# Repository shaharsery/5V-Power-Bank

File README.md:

# 5V rechargeable power bank (Work in progress)

This project is a 5V rechargeable power bank, intended for use with 1 Li-ion / Li-Pol 3.7V rechargeable battery cell.

The design supports up to 1A of charge current and up to 1A of output current.

The exact specification of this design are strongly related to the battery used and other elements such as components used, enclosure, wall adapter etc. 

This is an open source hardware (OSHW) project, licensed under the Creative Commons Attribution Share Alike 4.0 International license.
 
For more information read the LICENSE file in the master branch, and visit [creativecommons.org](https://creativecommons.org/)

**Please note that this project has not yet been manufactured or tested! USE AT YOUR OWN RISK!**

## Specifications 

#### Nominal ratings and parameters: 

Input Voltage: 5V

Output Voltage: 5V

Battery Cell: Li-ion / Li-Pol 3.7V 

Charge Current: 1A MAX (Adjustable)

Output Current: 1A MAX

#### Features:

The features below are based on the full BOM (without NC components), changing values of components and / or unplacing components may cause unintended behaviors.

\- Input connectors: USB Type-B Micro, solder pads.

\- Output connectors: USB Type-A port, solder pads. 

\- Battery cell protections: Overcharge voltage, overdischarge voltage, overcharge current, overdischarge current, over-temperature operation, ESD protection and reverse polarity protection.

** THIS DOESN'T MEAN NOTHING CAN GO WRONG, ALWAYS MAKE SURE YOU CONNECTED EVERYTHING CORRECTLY, BATTERIES CAN EXPLODE, BURN AND HARM YOU IF NOT PROPERLY USED **

\- Adjustable charge current by changing resistor value (R5)

\- 2 indication LEDs:

- Green LED to indicate charge completed (the green LED will turn off once the battery cell entered 2nd charge cycle).
	
- Blue LED to indicate input power to the PCB. 

Both LEDs will turn off when the power bank is removed from the wall adapter.

\- If the device is connected to a wall adapter a battery and a load, the load will be powered from the wall adapter and the battery will keep on charging, this might not work properly if the wall adapter rated current is not high enough (for MAX currents, the wall adapter should be capable of driving at least 2A)

## Notes

\- The design was created as an entry level design project, it was designed to allow for others to learn, work with and create.
 I wanted to keep the design pretty simple and to make it 'hand-solderable', that's why all passive components' packages are 0603 or larger and all ICs have lead pins,
 that way all components can be soldered using a solder iron and some basic skills.
 
 \- Through the design process I was aiming for the use of 18650 Li-ion battery cells, though it should work with any Li-ion / Li-Pol 3.7V battery, I plan on testing other battery cell packages once I'll have the PCBs for prototyping.
 
 \- Though all the components used in this project can be easily sourced from Digi-Key and Mouser, I tried to use components that can also be sourced through LCSC, Ebay or AliExpress, try to find a reliable distributor that suits your costs and needs.
 
 \- A lot of modifications can be made to reduce the cost of this design, consider the necessity of components according to your own use.
 
 \- I know some people would prefer the input connector to be Type-C, I might add another version of this design with Type-C connector later.
 
 \- I plan on creating 2 types of PCBs, one roughly the dimensions of a 18650 package, and one compact design that might be more suitable for flat battery packages.
 
 \- Please feel free to contact me if you have any question or remark, or if you found any mistake. I'll try to reply as fast as I can but I can't promise anything.
 
 \- Keep being awesome and help the OSHW community grow!

## Disclaimer

**Before you work with this project in any way, please make sure you understand what you are doing, electronics and batteries can be harmful and dangerous when not used properly.** 

**By using this project in any way you agree that you are using it at your own risk and you can't hold any one else accountable for any damage or harm that might be caused due to your use of this project.**

**Please note that this project has not yet been manufactured or tested! USE AT YOUR OWN RISK!**

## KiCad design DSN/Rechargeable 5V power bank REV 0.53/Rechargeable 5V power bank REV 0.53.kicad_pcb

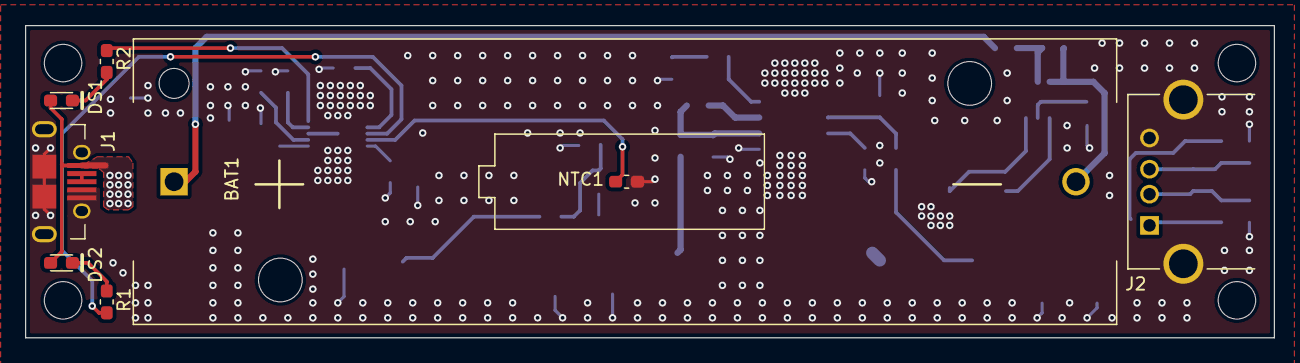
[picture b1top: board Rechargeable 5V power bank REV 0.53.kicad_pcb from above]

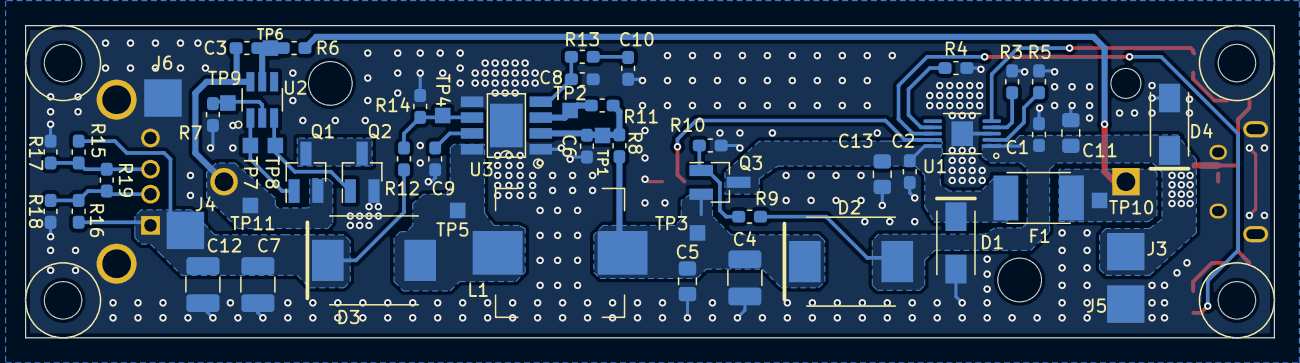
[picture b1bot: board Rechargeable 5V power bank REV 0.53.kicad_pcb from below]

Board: 2 copper layers, 100.0 x 25.0 mm, 69 parts (61 on the bottom side), 31 nets.

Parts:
BAT1: BAT_18650_HOLDER_THT
C1, C2, C6: CAPC_1uF_0603; CACP_0603_HandSolder
C3: CAPC_100nF_0603; CACP_0603_HandSolder
C4: CAPC_22uF_1210; CAPC_1210_HandSolder
C5, C11, C13: CAPC_10uF_0805; CAPC_0805_HandSolder
C7, C12: CAPC_10uF_1210; CAPC_1210_HandSolder
C8: CAPC_47pF_0603; CACP_0603_HandSolder
C9: CAPC_10nF_0603; CACP_0603_HandSolder
C10: CAPC_2.2nF_0603; CACP_0603_HandSolder
D1, D4: TVS_5V_9.2V_DO214AC; DO-214AC
D2, D3: Schottky_40V_5A_DO-214AB; DO-214AB
DS1: LEDC_BLUE_0603; LEDC_0603_HandSolder
DS2: LEDC_GREEN_0603; LEDC_0603_HandSolder
F1: PTC_POLYFUSE_8V_2A_1812; POLYFUSEC_1812
J1: Micro_USB_CONN; USB-TYPE-B_CONN_PORT
J2: USB-A_CONN; USB-TYPE-A_CONN_PORT
J3, J4, J5, J6: 1POS_CONN_PAD_30X30MM_H1MM; PAD_RECT_30X30
L1: INDC_10uH_CDRH104R; CDRH104R
MH1, MH2, MH3, MH4: M3C6_NP
NTC1: NTC_10K_3380K_0603; RESC_0603_HandSolder
Q1, Q2: NMOS_20V_3.6A_SOT-23-3; SOT-23_Handsoldering
Q3: PMOS_20V_4.2A_SOT-23-3; SOT-23_Handsoldering
R1, R2: RESC_470R_0603; RESC_0603_HandSolder
R3: RESC_2K_0603; RESC_0603_HandSolder
R4, R10, R11, R14, R15, R16, R17, R18: RESC_10K_0603; RESC_0603_HandSolder
R5: RESC_549R_0603; RESC_0603_HandSolder
R6: RESC_330R_0603; RESC_0603_HandSolder
R7: RESC_2K7_0603; RESC_0603_HandSolder
R8: RESC_10R_0603; RESC_0603_HandSolder
R9: RESC_1K_0603; RESC_0603_HandSolder
R12: RESC_30K1_0603; RESC_0603_HandSolder
R13: RESC_51K_0603; RESC_0603_HandSolder
R19: RESC_0R_0603; RESC_0603_HandSolder
TP1, TP2, TP3, TP4, TP5, TP6, TP7, TP8, TP9, TP10, TP11: TP_1.25X1.25_MM; TP_RECT_1.25X1.25
U1: BQ24090DGQR; BQ24090DGQR_MSOP-10
U2: AP9101C; AP9101C_SOT-23-6_Handsoldering
U3: PAM2421; PAM2421_SOIC-8-EP

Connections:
+VBAT_CELL: C2.2, C13.1, D1.K, F1.2, Q3.D, U1.10
/+VBAT: BAT1.+, F1.1, R6.2, TP10.1
/-VBAT: BAT1.-, C3.2, Q1.S, TP11.1, U2.6
/BLED: DS1.K, R2.2
/BOOST_COMP: C8.1, R13.1, U3.4
/BOOST_EN: R11.2, TP2.1, U3.3
/BOOST_FB: R12.2, R14.2, TP4.1, U3.6
/BOOST_IND: C4.1, C5.1, D2.K, L1.1, Q3.S, R8.1, TP3.1
/BOOST_SS: C9.1, U3.7
/BOOST_SW: D3.A, L1.2, TP5.1, U3.8
/BOOST_VIN: C6.2, R8.2, R11.1, TP1.1, U3.2
/CO: Q2.G, TP8.1, U2.3
/DO: Q1.G, TP7.1, U2.1
/GLED: DS2.K, R1.2
/ISET: R5.1, U1.2
/ISET2: R4.2, U1.7
/NTC: NTC1.1, U1.9
/PRETERM: R3.1, U1.4
/U2_VDD: C3.1, R6.1, TP6.1, U2.5
/VM: R7.1, TP9.1, U2.2
/~CHG: R1.1, U1.8
/~PG: R2.1, U1.5
GND: C1.2, C2.1, C4.2, C5.2, C6.1, C7.2, C8.2, C9.2, C10.2, C11.2, C12.2, C13.2, D1.A, D4.A, J1.4, J1.5, J1.6, J1.7, J1.8, J1.9, J1.10, J1.11, J2.4, J2.5, J2.6, J5.1, J6.1, NTC1.2, Q2.S, R3.2, R4.1, R5.2, R7.2, R10.1, R14.1, R17.1, R18.1, U1.3, U1.11, U3.1, U3.5, U3.9
unnamed: C10.1, R13.2
unnamed: J1.2, J1.3
unnamed: J2.2, R16.1, R18.2, R19.2
unnamed: J2.3, R15.1, R17.2, R19.1
unnamed: Q1.D, Q2.D
unnamed: Q3.G, R9.1, R10.2
VBUS: C1.1, C11.1, D2.A, D4.K, DS1.A, DS2.A, J1.1, J3.1, R9.2, U1.1
VOUT: C7.1, C12.1, D3.K, J2.1, J4.1, R12.1, R15.2, R16.2

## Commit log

2020-07-27 Create LICENSE
2020-07-28 Uploaded DSN files
2020-07-28 Changed some files in the directory
2020-08-07 UPLOAD REV 0.5
2020-08-07 Update and minor fix
2020-08-13 Updated all files
2020-08-13 Changed names for pictures
